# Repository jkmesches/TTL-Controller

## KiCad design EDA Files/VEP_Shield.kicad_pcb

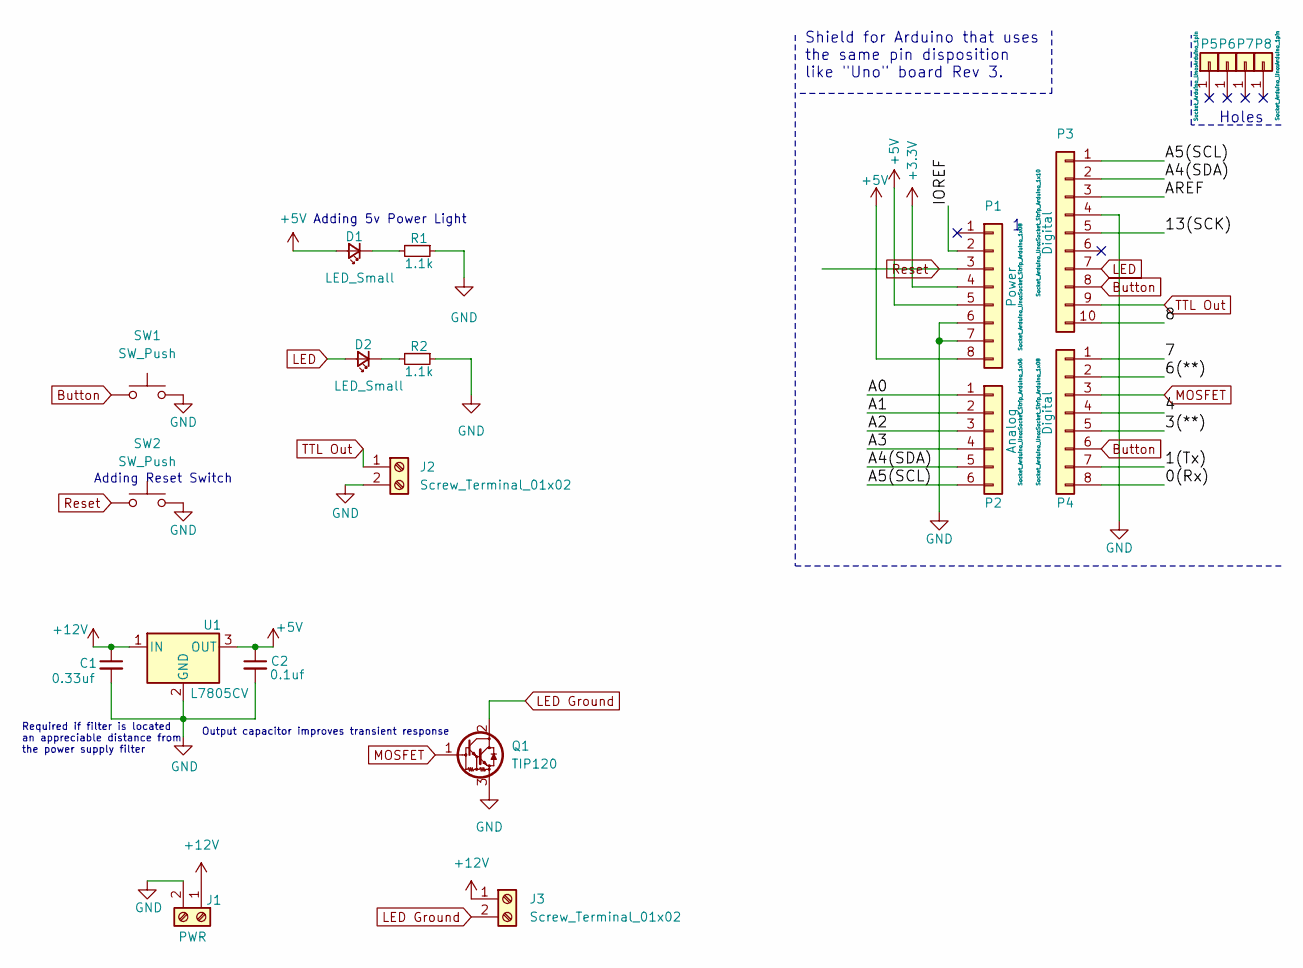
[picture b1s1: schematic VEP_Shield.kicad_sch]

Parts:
C1: 0.33uf; C_Disc_D3.0mm_W1.6mm_P2.50mm
C2: 0.1uf; C_Disc_D3.0mm_W1.6mm_P2.50mm
D1, D2: LED_Small; JST_PH_B2B-PH-K_1x02_P2.00mm_Vertical
J1: PWR; TerminalBlock_Phoenix_PT-1,5-2-5.0-H_1x02_P5.00mm_Horizontal
J2: Screw_Terminal_01x02; JST_PH_B2B-PH-K_1x02_P2.00mm_Vertical
J3: Screw_Terminal_01x02; TerminalBlock_Phoenix_PT-1,5-2-3.5-H_1x02_P3.50mm_Horizontal
P1: Power; Socket_Strip_Arduino_1x08
P2: Analog; Socket_Strip_Arduino_1x06
P3: Digital; Socket_Strip_Arduino_1x10
P4: Digital; Socket_Strip_Arduino_1x08
P5, P6, P7, P8: CONN_01X01; Arduino_1pin
Q1: TIP120; TO-220-3_Vertical
R1, R2: 1.1k; R_Axial_DIN0207_L6.3mm_D2.5mm_P7.62mm_Horizontal
SW1, SW2: SW_Push; JST_PH_B2B-PH-K_1x02_P2.00mm_Vertical
U1: L7805CV; TO-220-3_Vertical

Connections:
+3V3: P1.4
+5V: C2.1, D1.2 (A), P1.5, P1.8, U1.3 (OUT)
+12V: C1.1, J1.1, J3.1, U1.1 (IN)
/0(Rx): P4.8
/1(Tx): P4.7
/3(**): P4.5
/4: P4.4
/6(**): P4.2
/7: P4.1
/8: P3.10
/13(SCK): P3.5
/A0: P2.1
/A1: P2.2
/A2: P2.3
/A3: P2.4
/A4(SDA): P2.5, P3.2
/A5(SCL): P2.6, P3.1
/AREF: P3.3
/IOREF: P1.2
Button: P3.8, P4.6, SW1.1
GND: C1.2, C2.2, J1.2, J2.2, P1.6, P1.7, P3.4, Q1.3 (E), R1.1, R2.1, SW1.2, SW2.2, U1.2 (GND)
LED: D2.2 (A), P3.7
LED Ground: J3.2, Q1.2 (C)
MOSFET: P4.3, Q1.1 (B)
unnamed: D1.1 (K), R1.2
unnamed: D2.1 (K), R2.2
Reset: P1.3, SW2.1
TTL Out: J2.1, P3.9

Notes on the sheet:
Adding Reset Switch
Required if filter is located an appreciable distance from the power supply filter
Output capacitor improves transient response
Holes
Shield for Arduino that uses the same pin disposition like "Uno" board Rev 3.
Adding 5v Power Light

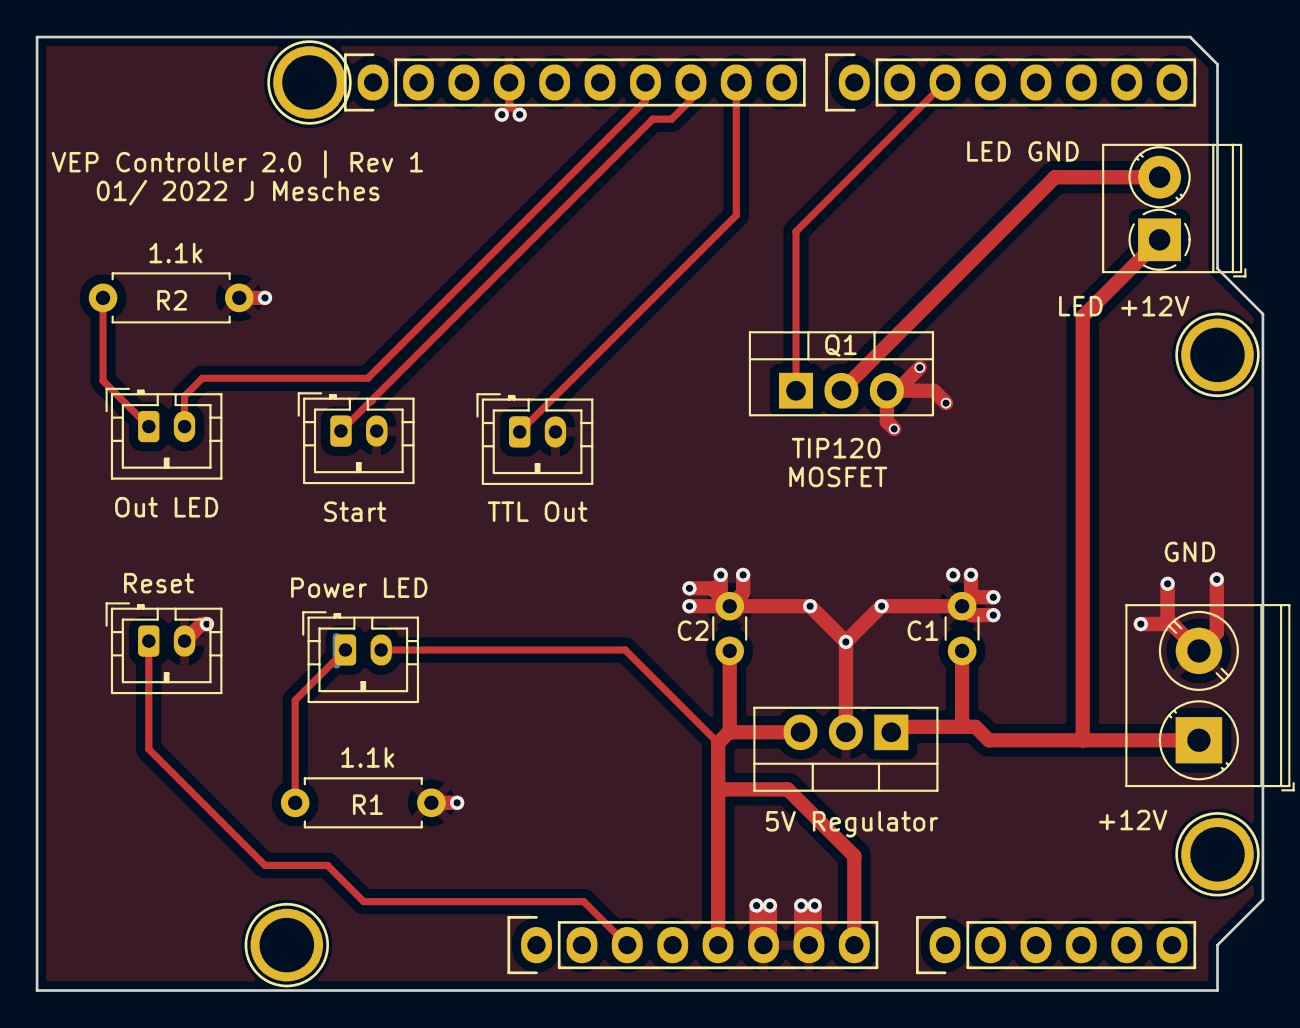
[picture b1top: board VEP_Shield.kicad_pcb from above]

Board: 2 copper layers, 68.6 x 53.3 mm, 21 parts (0 on the bottom side), 13 nets.

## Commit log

2022-01-24 Added Sliced Files
2022-01-24 Added Code
2022-01-24 Adding BOM
2022-01-24 Minor Edit
2022-01-28 Added original code
2022-02-03 Updated Code
2022-02-16 Updated Case Package
